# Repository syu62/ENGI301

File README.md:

# ENGI301
<ENGI301>
Respository for ENGI301 course work

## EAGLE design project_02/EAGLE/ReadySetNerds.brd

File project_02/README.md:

# Ready, Set, Nerds! PCB Design
This folder contains information for a PCB design for my ENGI301 project - Ready, Set, Nerds!

# Directory Folders
## docs
Includes mechanical diagrams, published schematic for the PCB, images of the top and bottom layer of the PCB, and bill of materials (BOM).

## EAGLE
Includes the EagleCAD files for the PCB design (lbr, sch, and brd).

## CAMOutput
Includes assembly, drillfiles, and gerberfiles generated from the PCB board on eagle.

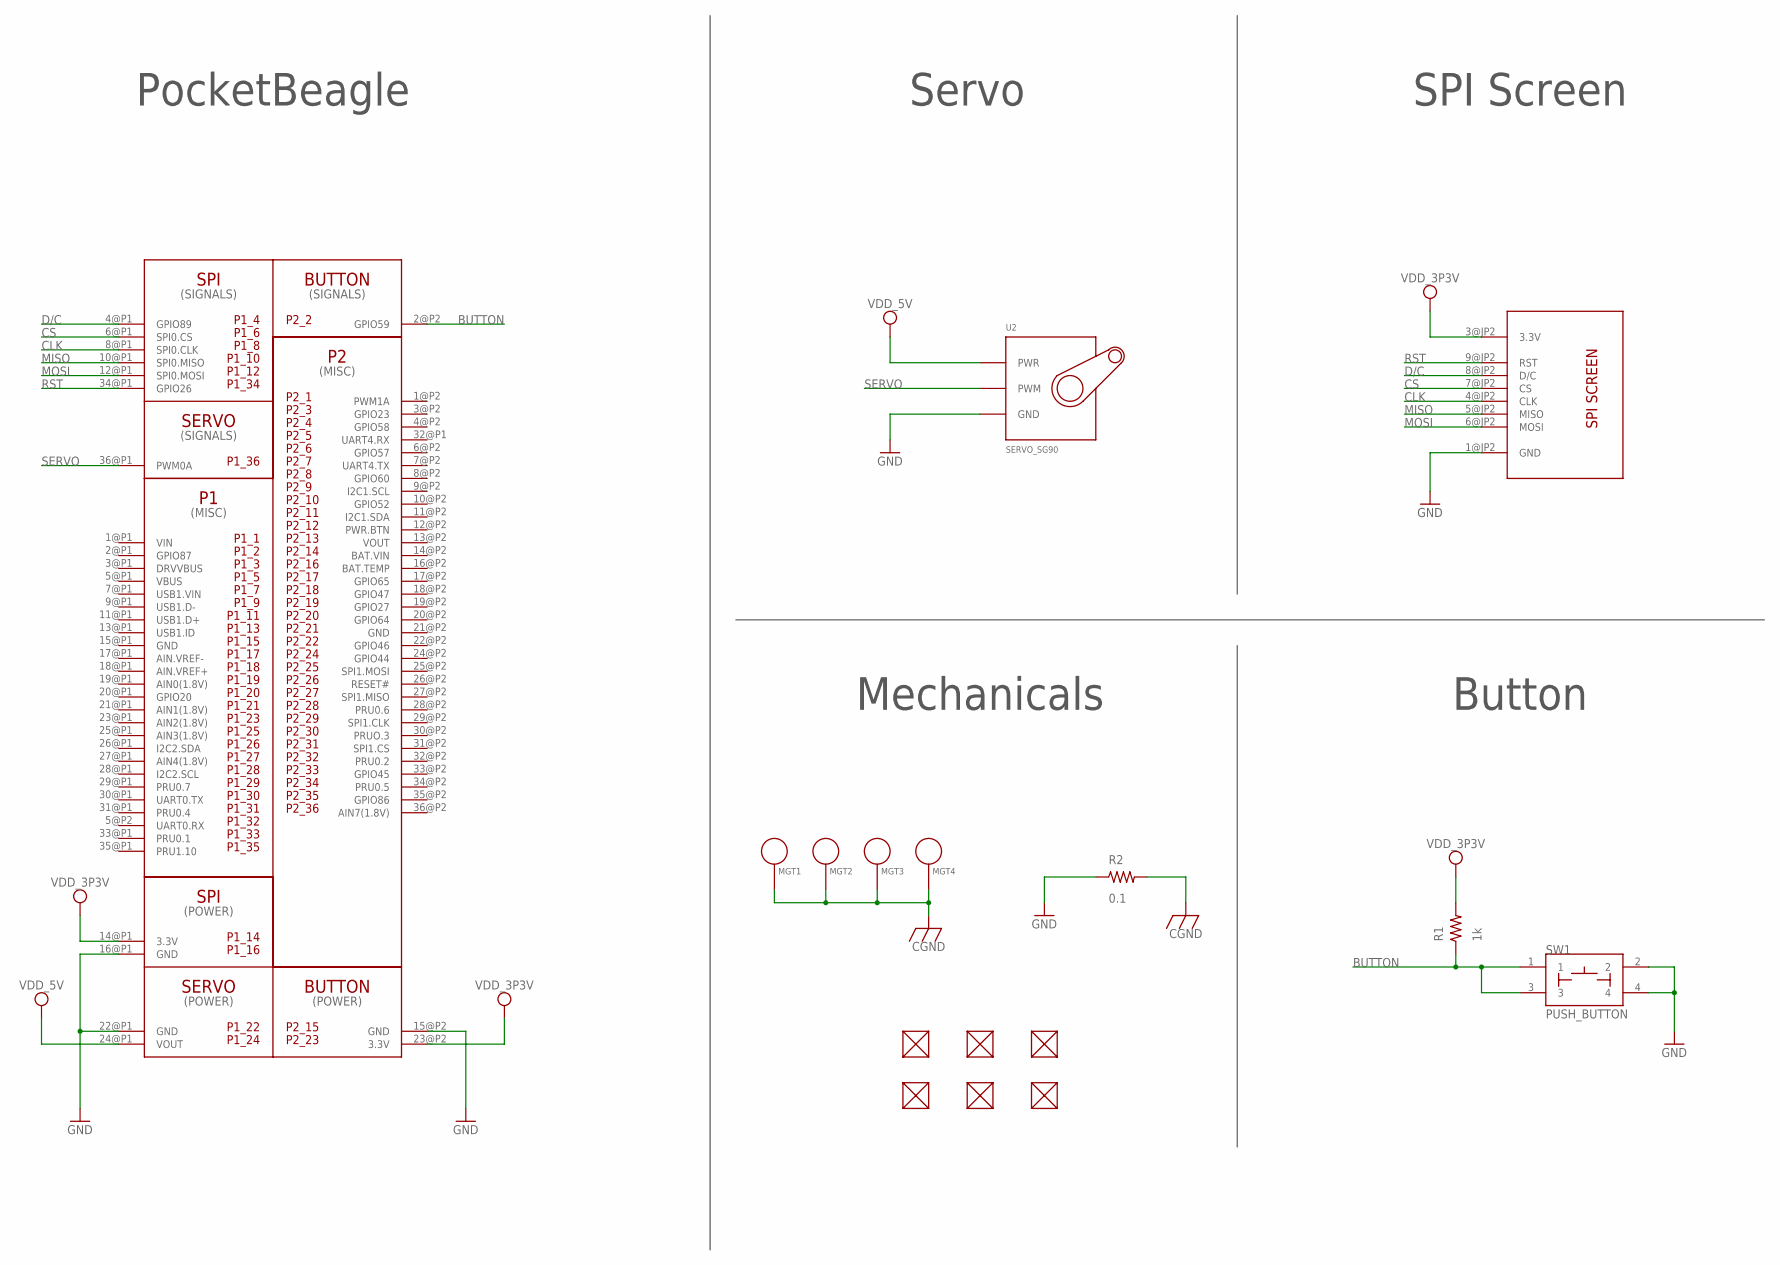
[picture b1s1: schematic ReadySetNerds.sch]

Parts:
FUD1, FUD2, FUD3, FUD4, FUD5, FUD6: FIDUCIAL; FIDUCIAL_40MIL
MGT1, MGT2, MGT3, MGT4: MOUNTING_HOLE
R1: 1k; R0603
R2: 0.1; R0603
SW1: PUSH_BUTTON; BUTTON_12.5MM
U2: SERVO_SG90; SERVO-X1
U$1: POCKETBEAGLE
U$2: SPISCREEN

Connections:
BUTTON: R1.1, SW1.1, SW1.3, U$1.2@P2 (GPIO59)
CGND: MGT1.P$1, MGT2.P$1, MGT3.P$1, MGT4.P$1, R2.2
CLK: U$1.8@P1 (SPI0.CLK), U$2.4@JP2 (CLK)
CS: U$1.6@P1 (SPI0.CS), U$2.7@JP2 (CS)
D/C: U$1.4@P1 (GPIO89), U$2.8@JP2 (D/C)
GND: R2.1, SW1.2, SW1.4, U2.GND, U$1.15@P2 (GND), U$1.16@P1 (GND), U$1.22@P1 (GND), U$2.1@JP2 (GND)
MISO: U$1.10@P1 (SPI0.MISO), U$2.5@JP2 (MISO)
MOSI: U$1.12@P1 (SPI0.MOSI), U$2.6@JP2 (MOSI)
RST: U$1.34@P1 (GPIO26), U$2.9@JP2 (RST)
SERVO: U2.SIG (PWM), U$1.36@P1 (PWM0A)
VDD_3P3V: R1.2, U$1.14@P1 (3.3V), U$1.23@P2 (3.3V), U$2.3@JP2 (3.3V)
VDD_5V: U2.PWR, U$1.24@P1 (VOUT)

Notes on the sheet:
PocketBeagle
Servo
SPI Screen
Button
Mechanicals

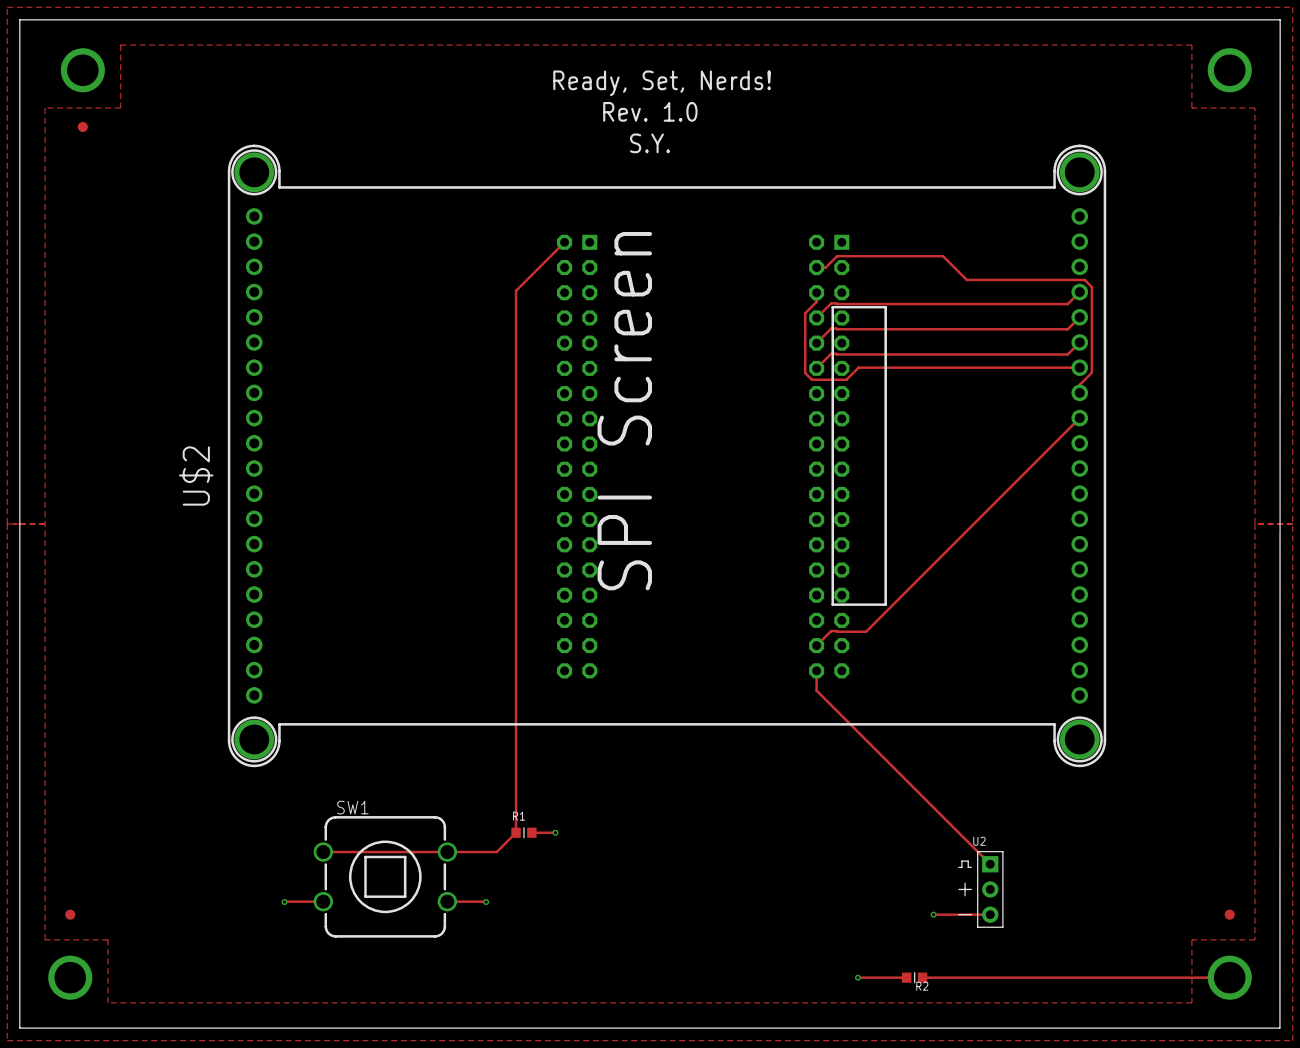
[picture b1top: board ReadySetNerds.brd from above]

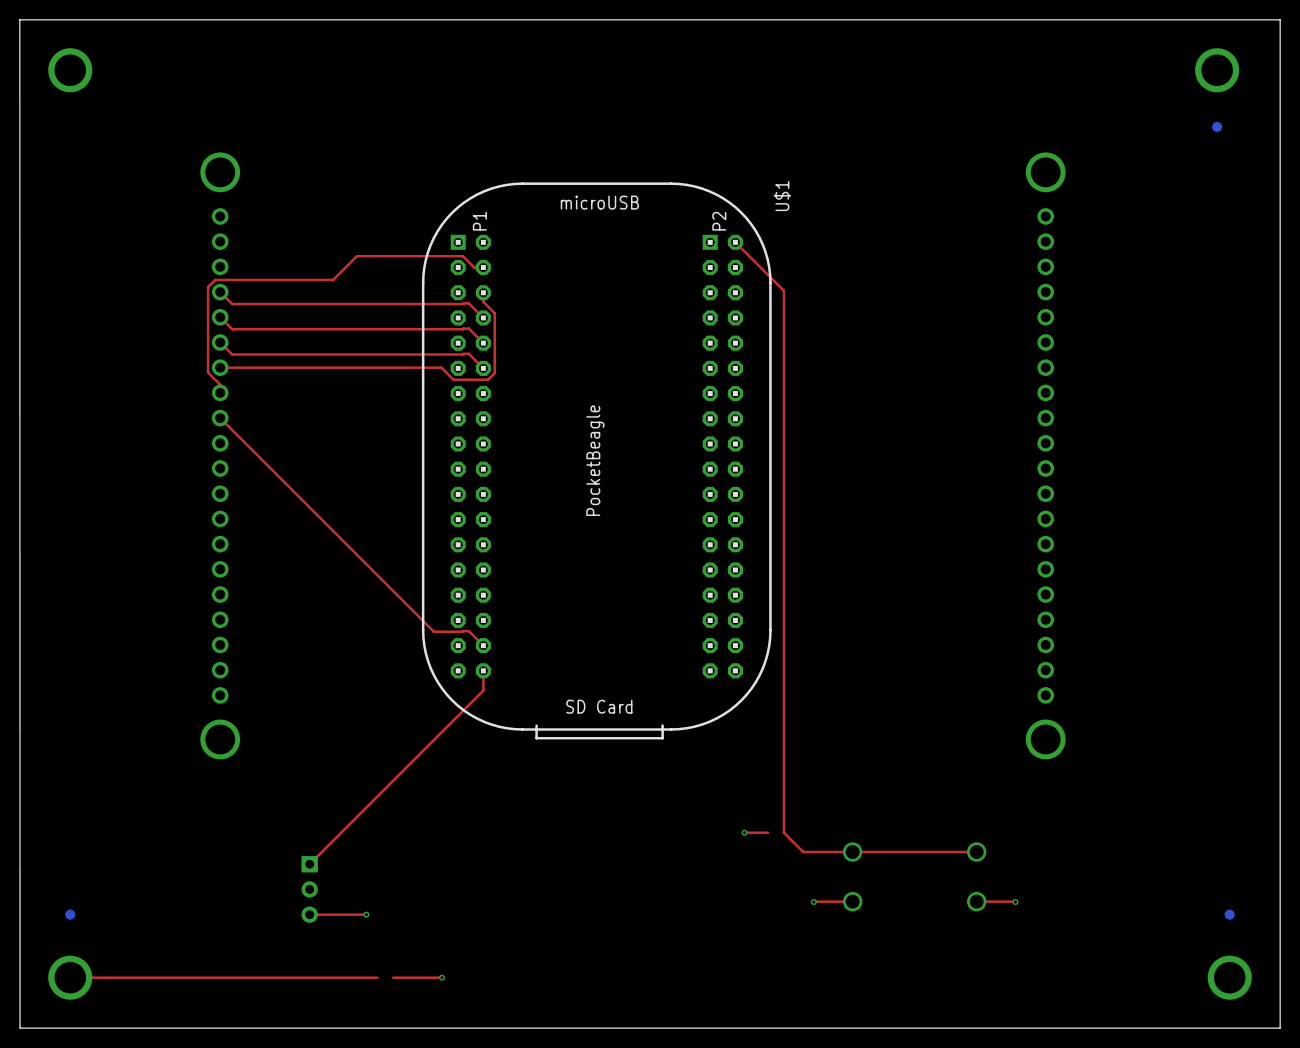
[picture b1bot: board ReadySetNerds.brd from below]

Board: 4 copper layers, 127.0 x 101.6 mm, 16 parts (4 on the bottom side), 12 nets.

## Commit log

2023-09-26 Create project_01
2023-09-26 Create filler
2023-09-29 Create Python Files
2023-09-29 Rename button (1).py to button.py
2023-09-29 Rename simple_calc (1).py to simple_calc.py
2023-10-01 Updated project proposal
2023-10-01 Old project proposal
2023-10-01 Original project proposal due 09-25-23
2023-10-13 Software Block Diagram 10-12-23
2023-10-13 Updated Project Proposal with Software Block Diagram
2023-11-18 Create SetGameCodeOnly
2023-12-16 Create project_02
2023-12-16 Create bluff
2023-12-16 Create ww
2023-12-16 Create Ready,Set,Nerds
2023-12-16 Create docs
2023-12-16 Create files
